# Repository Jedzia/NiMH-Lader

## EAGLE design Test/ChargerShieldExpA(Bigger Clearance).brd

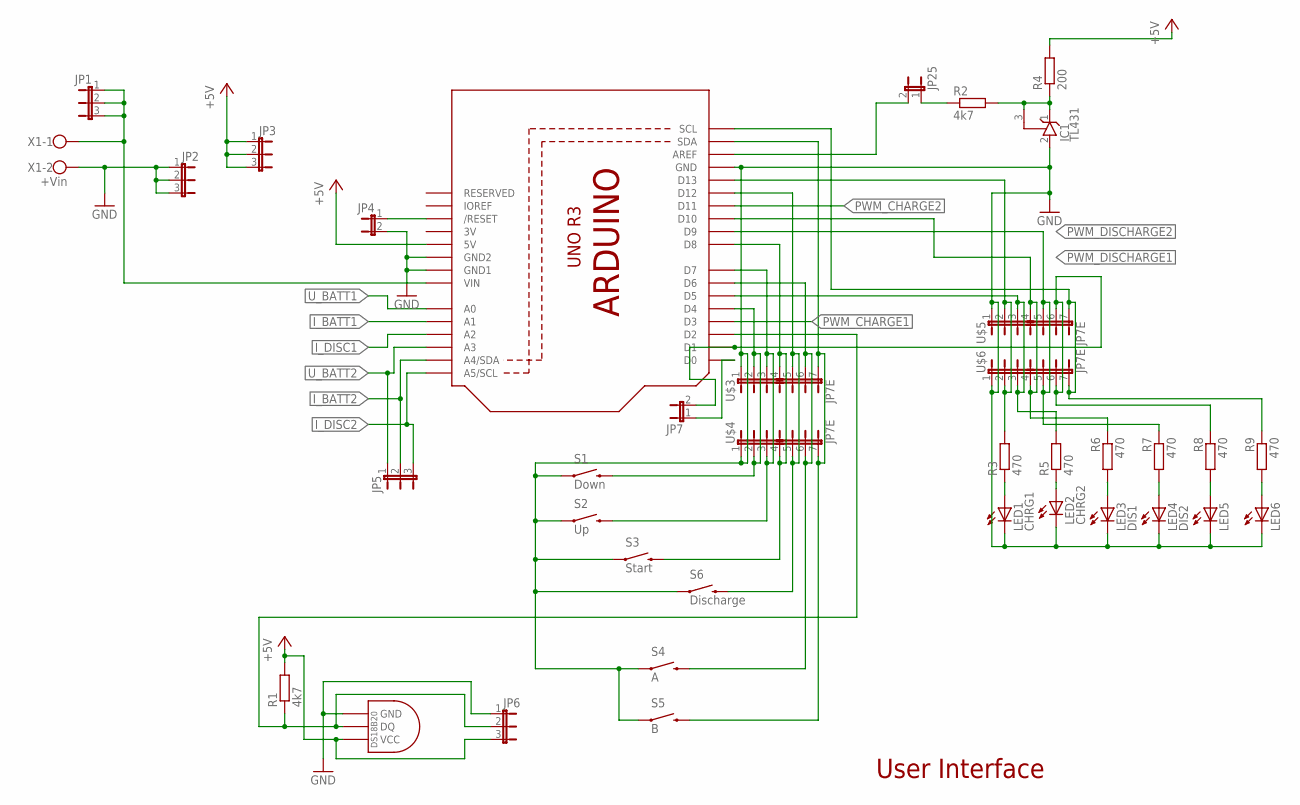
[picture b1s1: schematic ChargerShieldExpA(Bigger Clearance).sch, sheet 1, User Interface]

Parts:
IC1: TL431; TO92
JP1, JP2, JP3, JP5, JP6: JP2E; JP2
JP4, JP7, JP25: JP1E; JP1
LED1: CHRG1; LED5MM_BIG
LED2: CHRG2; LED5MM_BIG
LED3: DIS1; LED5MM_BIG
LED4: DIS2; LED5MM_BIG
LED5, LED6: LED5MM_BIG
R1: 4k7; 0204/7
R2: 4k7; 0207/10
R3: 470; 0207/12
R4: 200; 0204/7
R5, R6, R7: 470; 0207/10
R8, R9: 470; 0204/7
S1: Down; TACTILE-PTH-UMSE
S2: Up; TACTILE-PTH-UMSE
S3: Start; TACTILE-PTH-UMSE
S4: A; TACTILE-PTH-UMSE
S5: B; TACTILE-PTH-UMSE
S6: Discharge; TACTILE-PTH-UMSE
U$1: DS1820TO92; DS1820
U$2: ARDUINOR3BPLACE-LONG; ARDUINOR3-BPLACE-LONG
U$3, U$4, U$5, U$6: JP7E; JP7
X1: +Vin; W237-102

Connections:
3V: U$2.3V
+5V: JP3.1, JP3.2, JP3.3, JP6.3, R1.2, R4.2, U$1.VDD (VCC), U$2.5V; also elsewhere on the board
GND: IC1.2 (A), JP2.1, JP2.2, JP2.3, JP4.2, JP6.1, LED1.K (C), LED2.K (C), LED3.K (C), LED4.K (C), LED5.K (C), LED6.K (C), S1.1, S2.1, S3.1, S4.1, S5.1, S6.1, U$1.GND, U$2.GND, U$2.GND1, U$2.GND2, U$3.1, U$4.1, U$5.1, U$6.1, X1.2; also elsewhere on the board
I_BATT1: U$2.A1; also elsewhere on the board
I_BATT2: JP5.2, U$2.A4 (A4/SDA)
I_DISC1: U$2.A2; also elsewhere on the board
I_DISC2: JP5.3, U$2.A5 (A5/SCL)
unnamed: R3.2, U$2.D13, U$5.2, U$6.2
unnamed: LED1.A, R3.1
unnamed: JP6.2, R1.1, U$1.DQ, U$2.D2
unnamed: R5.2, U$2.D5, U$5.3, U$6.3
unnamed: LED3.A, R6.2
unnamed: LED4.A, R7.2
unnamed: S6.3 (2), U$2.D12, U$3.5, U$4.5
unnamed: LED2.A, R5.1
unnamed: S1.3 (2), U$2.D4, U$3.2, U$4.2
unnamed: IC1.1 (C), IC1.3 (R), R2.2, R4.1
unnamed: JP25.2, U$2.AREF
unnamed: S2.3 (2), U$2.D7, U$3.3, U$4.3
unnamed: S3.3 (2), U$2.D8, U$3.4, U$4.4
unnamed: S4.3 (2), U$2.D6, U$3.6, U$4.6
unnamed: S5.3 (2), U$2.SDA, U$3.7, U$4.7
unnamed: LED5.A, R8.2
unnamed: LED6.A, R9.2
unnamed: R9.1, U$2.SCL, U$5.7, U$6.7
unnamed: JP7.2, R8.1, U$2.D1, U$5.6, U$6.6
unnamed: JP7.1, U$2.D0
unnamed: JP4.1, U$2.RESET (/RESET)
unnamed: JP25.1, R2.1
PWM_CHARGE1: U$2.D3; also elsewhere on the board
PWM_CHARGE2: U$2.D11; also elsewhere on the board
PWM_DISCHARGE1: R6.1, U$2.D10, U$5.4, U$6.4; also elsewhere on the board
PWM_DISCHARGE2: R7.1, U$2.D9, U$5.5, U$6.5
U_BATT1: U$2.A0; also elsewhere on the board
U_BATT2: JP5.1, U$2.A3
VIN: JP1.1, JP1.2, JP1.3, U$2.VIN, X1.1; also elsewhere on the board

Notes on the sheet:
User Interface

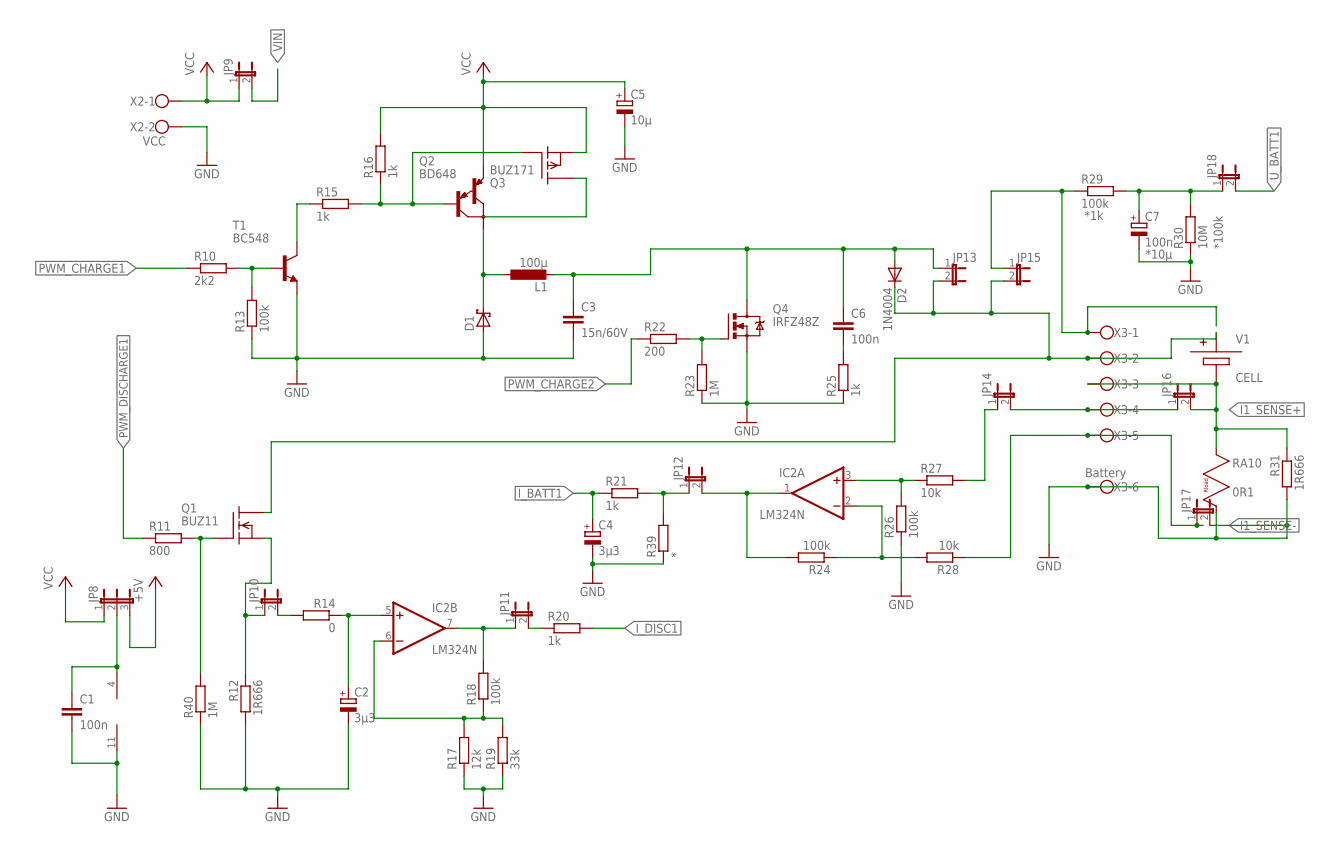
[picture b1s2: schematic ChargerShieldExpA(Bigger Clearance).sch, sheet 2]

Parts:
C1, C6: 100n; C025_050-025X075
C2, C4: 3µ3; E5-5
C3: 15n/60V; C025_050-025X075
C5: 10µ; E5-5
C7: 100n; E5-5
D1: SCHOTTKY-DIODEDO35-7; DO35-7
D2: 1N4004; DO41-10
IC2: LM324N; DIL14
JP8: JP2E; JP2
JP9, JP10, JP11, JP12, JP13, JP14, JP15, JP16, JP17, JP18: JP1E; JP1
L1: 100µ; 0207/12
Q1: BUZ11; TO220
Q2: BD648; TO220
Q3: BUZ171; TO220
Q4: IRFZ48Z; TO220BH
R10: 2k2; 0207/15
R11: 800; 0204/7
R12, R31: 1R666; 0414/15
R13, R18: 100k; 0207/10
R14: 0; 0207/10
R15, R16, R25: 1k; 0207/10
R17: 12k; 0207/10
R19: 33k; 0207/10
R20: 1k; 0207/15
R21: 1k; 0204/7
R22: 200; 0207/12
R23, R40: 1M; 0207/10
R24, R26: 100k; 0204/7
R27, R28: 10k; 0207/10
R29: 100k; 0207/12
R30: 10M; 0207/10
R39: *; 0204/7
T1: BC548; TO92
X2: VCC; W237-102
X3: Battery; W237-6

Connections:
+5V: JP8.3; also elsewhere on the board
GND: C1.2, C2.-, C3.2, C4.-, C5.-, C7.-, D1.A, IC2.11 (V-), JP17.2, Q4.S, R12.2, R13.1, R17.1, R19.1, R23.1, R25.1, R26.1, R30.1, R31.2, R39.1, R40.1, T1.1 (E), X2.2, X3.6; also elsewhere on the board
I1_SENSE+: JP16.2, R31.1, X3.3
I1_SENSE-: JP17.1, R28.1, X3.5
I_BATT1: C4.+, R21.1; also elsewhere on the board
I_DISC1: R20.2; also elsewhere on the board
unnamed: C7.+, JP18.1, R29.2, R30.2
unnamed: C1.1, IC2.4 (V+), JP8.2
unnamed: R10.2, R13.2, T1.2 (B)
unnamed: R15.1, T1.3 (C)
unnamed: Q2.1 (B), Q3.1 (G), R15.2, R16.1
unnamed: JP15.1, R29.1, X3.1
unnamed: D1.C, L1.1, Q2.2 (C)
unnamed: C3.1, C6.1, D2.A, JP13.1, L1.2, Q4.D
unnamed: IC2.1 (OUT), JP12.2, R24.2
unnamed: D2.C, JP13.2, JP15.2, Q1.2 (D), X3.2
unnamed: IC2.2 (-IN), R24.1, R28.2
unnamed: IC2.3 (+IN), R26.2, R27.1
unnamed: IC2.6 (-IN), R17.2, R18.1, R19.2
unnamed: IC2.7 (OUT), JP11.1, R18.2
unnamed: Q1.1 (G), R11.2, R40.2
unnamed: JP14.1, R27.2
unnamed: JP10.1, Q1.3 (S), R12.1
unnamed: C2.+, IC2.5 (+IN), R14.1
unnamed: JP12.1, R21.2, R39.2
unnamed: JP10.2, R14.2
unnamed: JP11.2, R20.1
unnamed: C6.2, R25.2
unnamed: Q4.G, R22.2, R23.2
unnamed: JP14.2, JP16.1, X3.4
PWM_CHARGE1: R10.1; also elsewhere on the board
PWM_CHARGE2: R22.1; also elsewhere on the board
PWM_DISCHARGE1: R11.1; also elsewhere on the board
U_BATT1: JP18.2; also elsewhere on the board
VCC: C5.+, JP8.1, JP9.1, Q2.3 (E), Q3.3 (S), R16.2, X2.1; also elsewhere on the board
VIN: JP9.2; also elsewhere on the board

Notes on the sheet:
*1k
*10µ
*100k

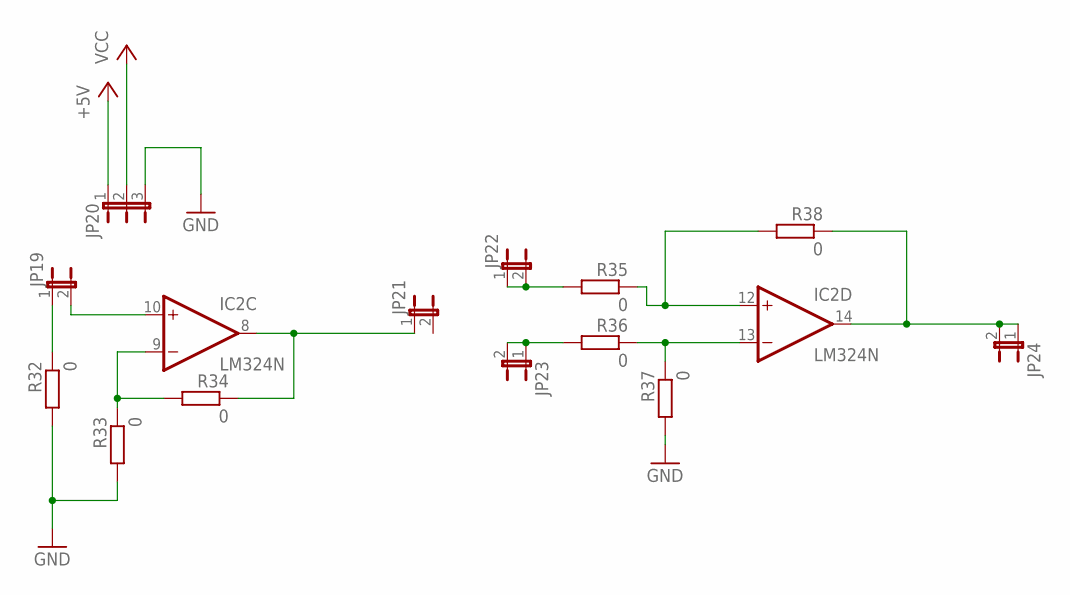
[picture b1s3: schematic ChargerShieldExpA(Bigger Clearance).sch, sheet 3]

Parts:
IC2: LM324N; DIL14
JP19, JP21, JP22, JP23, JP24: JP1E; JP1
JP20: JP2E; JP2
R32, R33, R36, R37, R38: 0; 0204/7
R34: 0; 0204V
R35: 0; 0207/10

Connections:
+5V: JP20.1; also elsewhere on the board
GND: JP20.3, R32.2, R33.2, R37.2; also elsewhere on the board
unnamed: IC2.8 (OUT), JP21.1, R34.1
unnamed: IC2.13 (-IN), R36.1, R37.1
unnamed: IC2.10 (+IN), JP19.2
unnamed: JP19.1, R32.1
unnamed: IC2.12 (+IN), R35.1, R38.2
unnamed: JP22.1, JP22.2, R35.2
unnamed: JP23.1, JP23.2, R36.2
unnamed: IC2.14 (OUT), JP24.1, JP24.2, R38.1
unnamed: IC2.9 (-IN), R33.1, R34.2
VCC: JP20.2; also elsewhere on the board

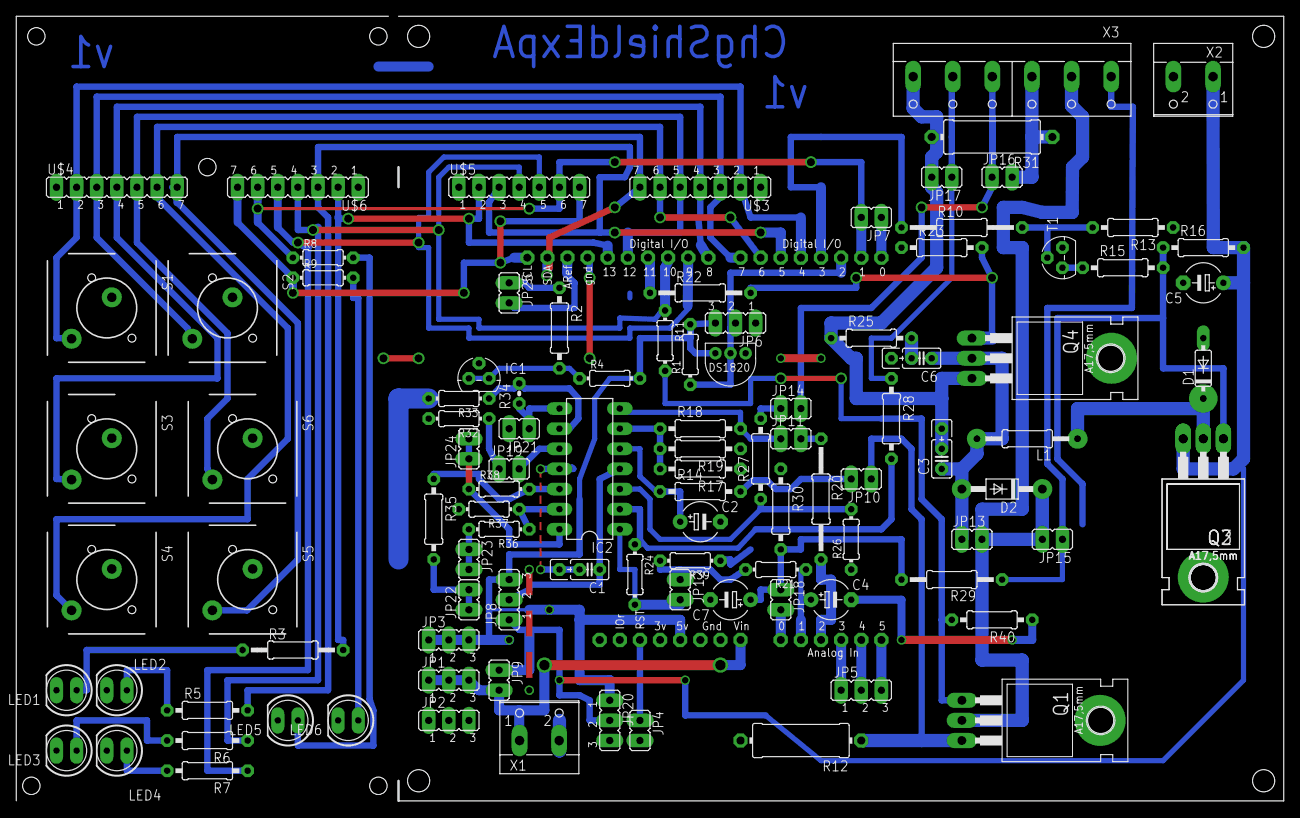
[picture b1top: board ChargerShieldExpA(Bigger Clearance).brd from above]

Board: 2 copper layers, 159.8 x 99.0 mm, 103 parts (0 on the bottom side), 71 nets.

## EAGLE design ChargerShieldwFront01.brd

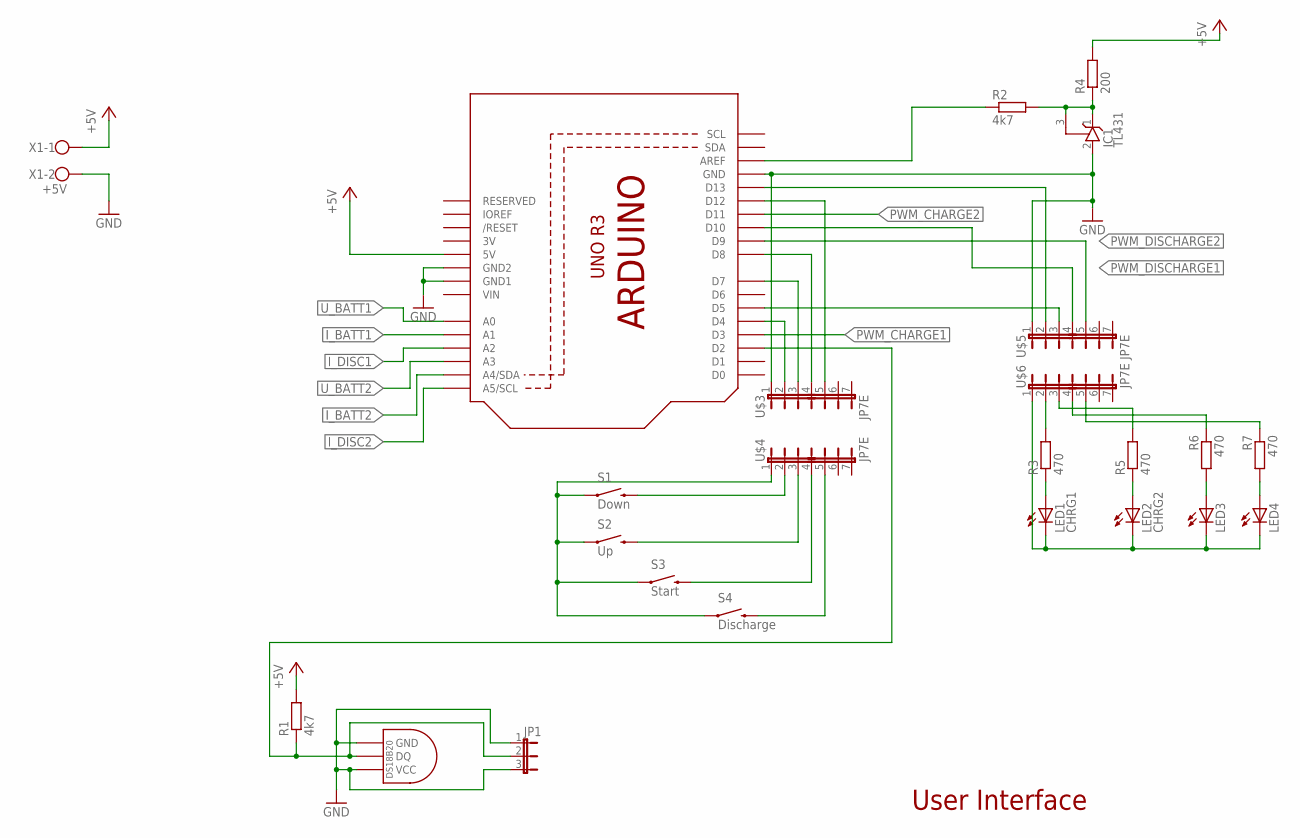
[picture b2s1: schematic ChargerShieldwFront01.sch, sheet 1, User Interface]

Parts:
IC1: TL431; TO92
JP1: JP2E; JP2
LED1: CHRG1; LED5MM_BIG
LED2: CHRG2; LED5MM_BIG
LED3, LED4: LED5MM_BIG
R1: 4k7; 0204/7
R2: 4k7; 0207/10
R3: 470; 0207/12
R4: 200; 0204/7
R5, R6, R7: 470; 0207/10
S1: Down; TACTILE-PTH
S2: Up; TACTILE-PTH
S3: Start; TACTILE-PTH
S4: Discharge; TACTILE-PTH
U$1: DS1820TO92; DS1820
U$2: ARDUINOR3BPLACE-LONG; ARDUINOR3-BPLACE-LONG
U$3, U$4, U$5, U$6: JP7E; JP7
X1: +5V; W237-102

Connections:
3V: U$2.3V
+5V: R1.2, R4.2, U$2.5V, X1.1; also elsewhere on the board
GND: IC1.2 (A), JP1.1, JP1.3, U$1.GND, U$1.VDD (VCC), U$2.GND, U$2.GND1, U$2.GND2, U$3.1, U$5.1, X1.2; also elsewhere on the board
GND2: LED1.K (C), LED2.K (C), LED3.K (C), LED4.K (C), S1.1, S2.1, S3.1, S4.1, U$4.1, U$6.1
I_BATT1: U$2.A1; also elsewhere on the board
I_BATT2: U$2.A4 (A4/SDA); also elsewhere on the board
I_DISC1: U$2.A2; also elsewhere on the board
I_DISC2: U$2.A5 (A5/SCL); also elsewhere on the board
unnamed: U$2.D13, U$5.2
unnamed: LED1.A, R3.1
unnamed: S1.3 (2), U$4.2
unnamed: S2.3 (2), U$4.3
unnamed: JP1.2, R1.1, U$1.DQ, U$2.D2
unnamed: U$2.D5, U$5.3
unnamed: LED3.A, R6.2
unnamed: LED4.A, R7.2
unnamed: S3.3 (2), U$4.4
unnamed: U$2.D12, U$3.5
unnamed: LED2.A, R5.1
unnamed: U$2.D4, U$3.2
unnamed: IC1.1 (C), IC1.3 (R), R2.2, R4.1
unnamed: R2.1, U$2.AREF
unnamed: U$2.D7, U$3.3
unnamed: U$2.D8, U$3.4
unnamed: S4.3 (2), U$4.5
unnamed: R5.2, U$6.3
unnamed: R3.2, U$6.2
unnamed: R6.1, U$6.4
unnamed: R7.1, U$6.5
PWM_CHARGE1: U$2.D3; also elsewhere on the board
PWM_CHARGE2: U$2.D11; also elsewhere on the board
PWM_DISCHARGE1: U$2.D10, U$5.4; also elsewhere on the board
PWM_DISCHARGE2: U$2.D9, U$5.5; also elsewhere on the board
U_BATT1: U$2.A0; also elsewhere on the board
U_BATT2: U$2.A3; also elsewhere on the board
VIN: U$2.VIN

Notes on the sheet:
User Interface

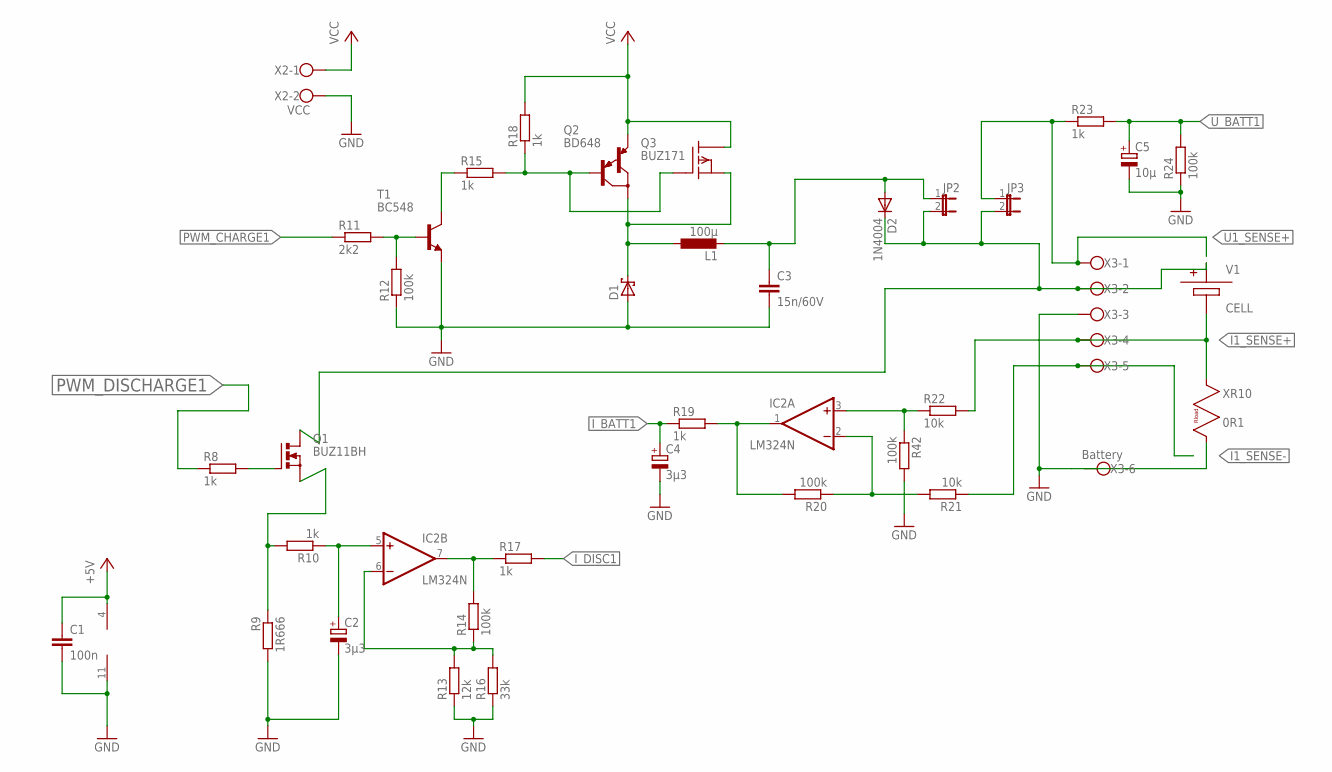
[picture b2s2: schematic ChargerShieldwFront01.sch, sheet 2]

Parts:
C1: 100n; C025_050-025X075
C2, C4: 3µ3; E5-5
C3: 15n/60V; C025_050-025X075
C5: 10µ; E5-5
D1: SCHOTTKY-DIODEDO35-7; DO35-7
D2: 1N4004; DO41-10
IC2: LM324N; DIL14
JP2, JP3: JP1E; JP1
L1: 100µ; 0207/12
Q1: BUZ11BH; TO220BH
Q2: BD648; TO220
Q3: BUZ171; TO220
R8, R19: 1k; 0207/12
R9: 1R666; 0414/15
R10, R15, R18, R23: 1k; 0207/10
R11: 2k2; 0207/10
R12, R20, R42: 100k; 0204/7
R13: 12k; 0207/10
R14, R24: 100k; 0207/10
R16: 33k; 0207/10
R17: 1k; 0207/15
R21: 10k; 0207/12
R22: 10k; 0207/10
T1: BC548; TO92
X2: VCC; W237-102
X3: Battery; W237-6

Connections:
+5V: C1.1, IC2.4 (V+); also elsewhere on the board
GND: C1.2, C2.-, C3.2, C4.-, C5.-, D1.A, IC2.11 (V-), R9.2, R12.1, R13.1, R16.1, R24.1, R42.2, T1.1 (E), X2.2, X3.3, X3.6; also elsewhere on the board
I1_SENSE+: R22.2, X3.4
I1_SENSE-: R21.1, X3.5
I_BATT1: C4.+, R19.1; also elsewhere on the board
I_DISC1: R17.2; also elsewhere on the board
unnamed: R11.2, R12.2, T1.2 (B)
unnamed: R15.1, T1.3 (C)
unnamed: Q2.1 (B), Q3.1 (G), R15.2, R18.1
unnamed: D1.C, L1.1, Q2.2 (C), Q3.3 (S)
unnamed: C3.1, D2.A, JP2.1, L1.2
unnamed: IC2.1 (OUT), R19.2, R20.2
unnamed: D2.C, JP2.2, JP3.2, Q1.D, X3.2
unnamed: IC2.2 (-IN), R20.1, R21.2
unnamed: IC2.3 (+IN), R22.1, R42.1
unnamed: IC2.6 (-IN), R13.2, R14.1, R16.2
unnamed: IC2.7 (OUT), R14.2, R17.1
unnamed: Q1.G, R8.2
unnamed: Q1.S, R9.1, R10.2
unnamed: C2.+, IC2.5 (+IN), R10.1
PWM_CHARGE1: R11.1; also elsewhere on the board
PWM_DISCHARGE1: R8.1; also elsewhere on the board
U1_SENSE+: JP3.1, R23.1, X3.1
U_BATT1: C5.+, R23.2, R24.2; also elsewhere on the board
VCC: Q2.3 (E), Q3.2 (D), R18.2, X2.1; also elsewhere on the board

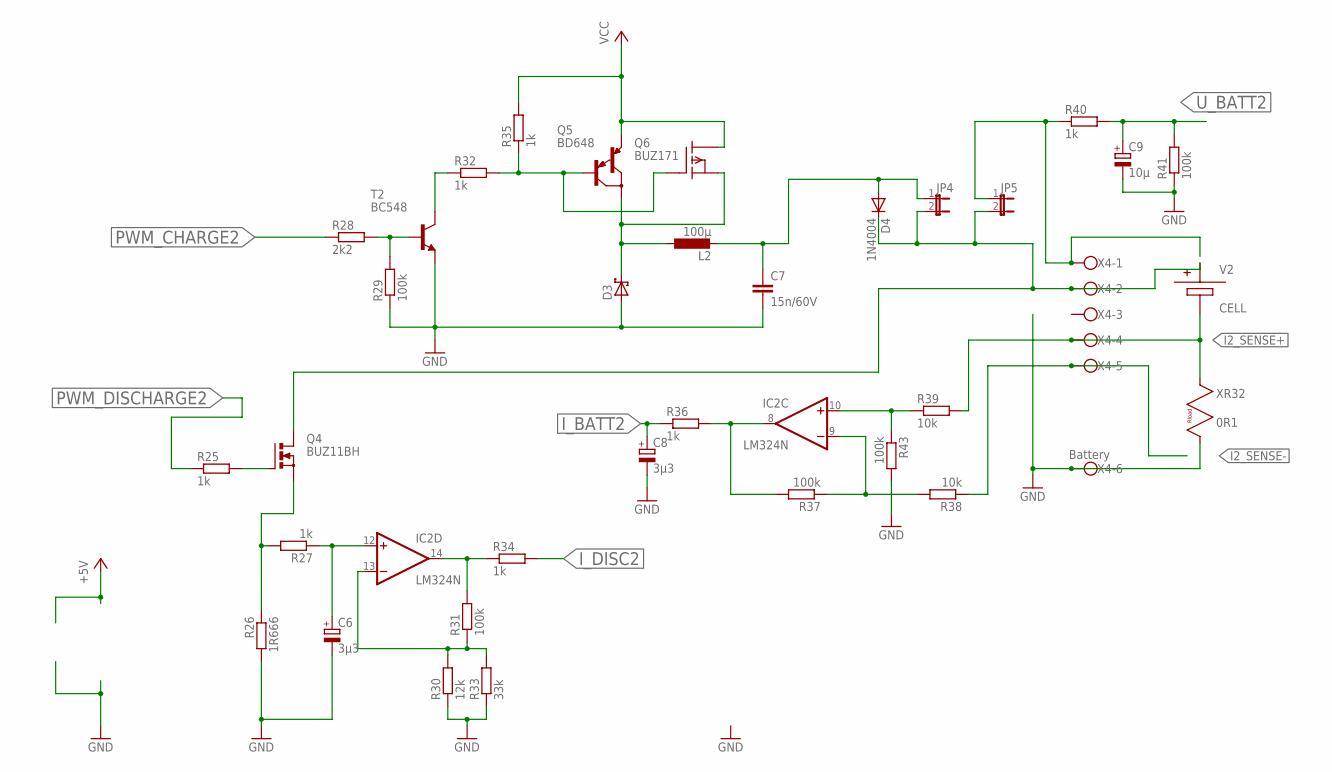
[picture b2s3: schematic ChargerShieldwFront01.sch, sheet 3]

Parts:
C6, C8: 3µ3; E5-5
C7: 15n/60V; C025_050-025X075
C9: 10µ; E5-5
D3: SCHOTTKY-DIODEDO35-7; DO35-7
D4: 1N4004; DO41-10
IC2: LM324N; DIL14
JP4, JP5: JP1E; JP1
L2: 100µ; 0207/12
Q4: BUZ11BH; TO220BH
Q5: BD648; TO220
Q6: BUZ171; TO220
R25, R32, R35, R40: 1k; 0207/10
R26: 1R666; 0414/15
R27, R36: 1k; 0207/12
R28: 2k2; 0207/15
R29, R37: 100k; 0204/7
R30: 12k; 0207/10
R31, R41, R43: 100k; 0207/10
R33: 33k; 0207/10
R34: 1k; 0207/15
R38: 10k; 0207/15
R39: 10k; 0207/10
T2: BC548; TO92
X4: Battery; W237-6

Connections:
GND: C6.-, C7.2, C8.-, C9.-, D3.A, R26.2, R29.1, R30.1, R33.1, R41.1, R43.2, T2.1 (E), X4.6; also elsewhere on the board
I2_SENSE+: R39.2, X4.4
I2_SENSE-: R38.1, X4.5
I_BATT2: C8.+, R36.1; also elsewhere on the board
I_DISC2: R34.2; also elsewhere on the board
unnamed: R28.2, R29.2, T2.2 (B)
unnamed: R32.1, T2.3 (C)
unnamed: Q5.1 (B), Q6.1 (G), R32.2, R35.1
unnamed: D3.C, L2.1, Q5.2 (C), Q6.3 (S)
unnamed: C7.1, D4.A, JP4.1, L2.2
unnamed: IC2.8 (OUT), R36.2, R37.2
unnamed: IC2.9 (-IN), R37.1, R38.2
unnamed: D4.C, JP4.2, JP5.2, Q4.D, X4.2
unnamed: JP5.1, R40.1, X4.1
unnamed: IC2.10 (+IN), R39.1, R43.1
unnamed: IC2.13 (-IN), R30.2, R31.1, R33.2
unnamed: IC2.14 (OUT), R31.2, R34.1
unnamed: Q4.G, R25.2
unnamed: Q4.S, R26.1, R27.2
unnamed: C6.+, IC2.12 (+IN), R27.1
PWM_CHARGE2: R28.1; also elsewhere on the board
PWM_DISCHARGE2: R25.1; also elsewhere on the board
U_BATT2: C9.+, R40.2, R41.2; also elsewhere on the board
VCC: Q5.3 (E), Q6.2 (D), R35.2; also elsewhere on the board

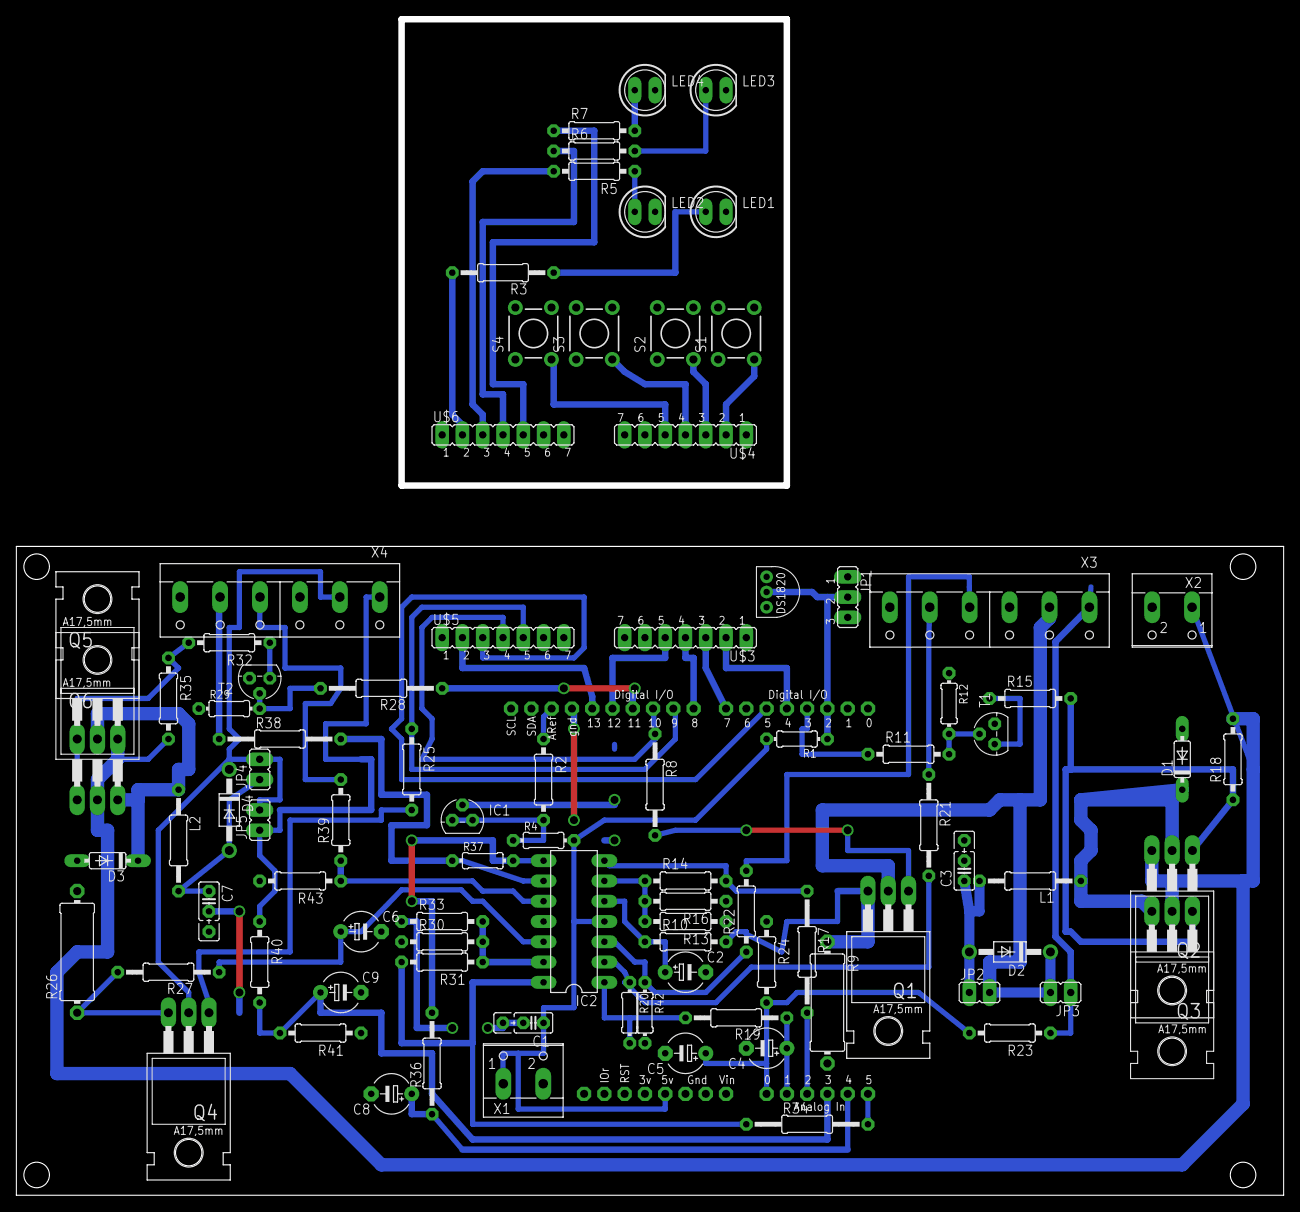
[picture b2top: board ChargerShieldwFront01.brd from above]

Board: 2 copper layers, 158.0 x 147.0 mm, 91 parts (0 on the bottom side), 69 nets.

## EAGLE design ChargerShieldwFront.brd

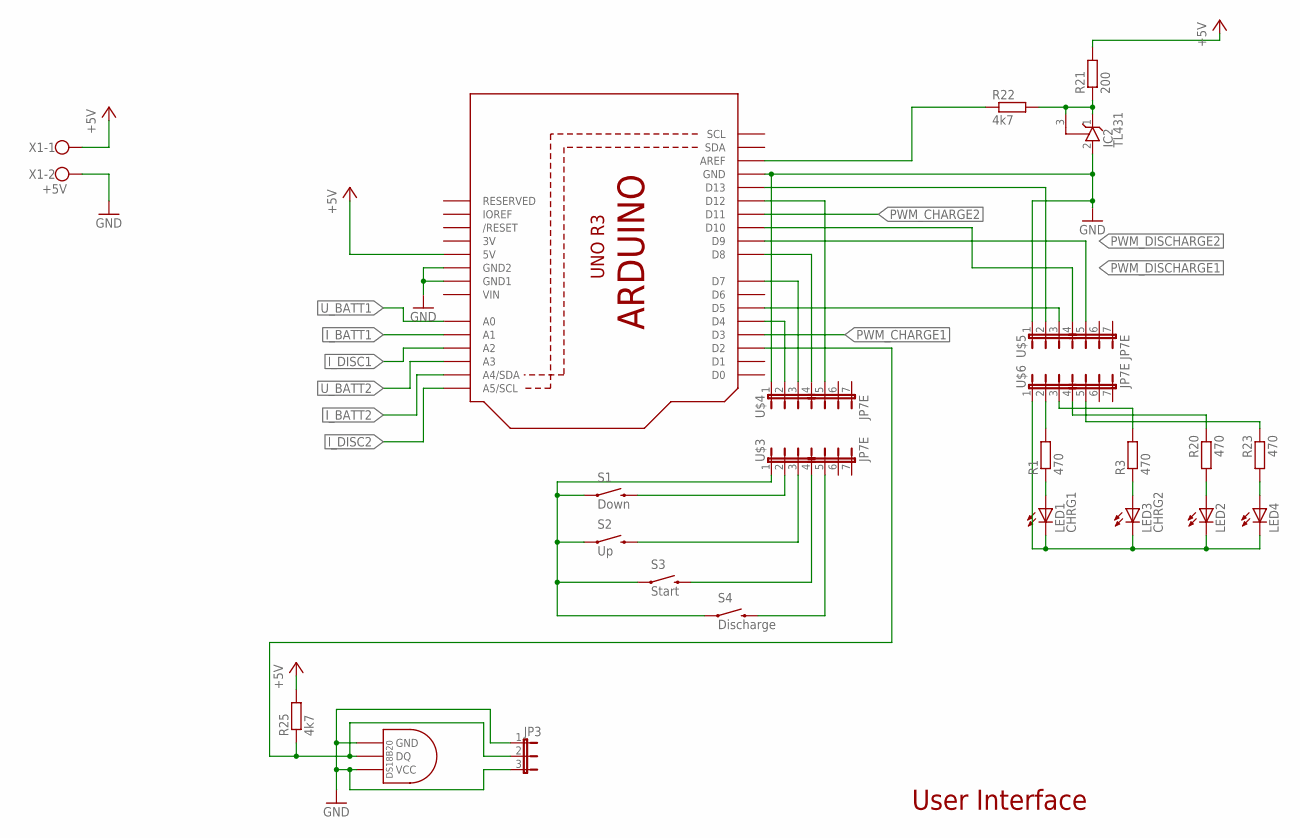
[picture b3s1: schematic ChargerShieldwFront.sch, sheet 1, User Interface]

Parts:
IC2: TL431; TO92
JP3: JP2E; JP2
LED1: CHRG1; LED5MM_BIG
LED2, LED4: LED5MM_BIG
LED3: CHRG2; LED5MM_BIG
R1: 470; 0207/12
R3, R20, R23: 470; 0207/10
R21: 200; 0204/7
R22: 4k7; 0207/10
R25: 4k7; 0204/7
S1: Down; TACTILE-PTH
S2: Up; TACTILE-PTH
S3: Start; TACTILE-PTH
S4: Discharge; TACTILE-PTH
U$1: ARDUINOR3BPLACE-LONG; ARDUINOR3-BPLACE-LONG
U$2: DS1820TO92; DS1820
U$3, U$4, U$5, U$6: JP7E; JP7
X1: +5V; W237-102

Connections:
3V: U$1.3V
+5V: R21.2, R25.2, U$1.5V, X1.1; also elsewhere on the board
GND: IC2.2 (A), JP3.1, JP3.3, U$1.GND, U$1.GND1, U$1.GND2, U$2.GND, U$2.VDD (VCC), U$4.1, U$5.1, X1.2; also elsewhere on the board
GND2: LED1.K (C), LED2.K (C), LED3.K (C), LED4.K (C), S1.1, S2.1, S3.1, S4.1, U$3.1, U$6.1
I_BATT1: U$1.A1; also elsewhere on the board
I_BATT2: U$1.A4 (A4/SDA)
I_DISC1: U$1.A2; also elsewhere on the board
I_DISC2: U$1.A5 (A5/SCL)
unnamed: U$1.D13, U$5.2
unnamed: LED1.A, R1.1
unnamed: S1.3 (2), U$3.2
unnamed: S2.3 (2), U$3.3
unnamed: JP3.2, R25.1, U$1.D2, U$2.DQ
unnamed: U$1.D5, U$5.3
unnamed: LED2.A, R20.2
unnamed: LED4.A, R23.2
unnamed: S3.3 (2), U$3.4
unnamed: U$1.D12, U$4.5
unnamed: LED3.A, R3.1
unnamed: U$1.D4, U$4.2
unnamed: IC2.1 (C), IC2.3 (R), R21.1, R22.2
unnamed: R22.1, U$1.AREF
unnamed: U$1.D7, U$4.3
unnamed: U$1.D8, U$4.4
unnamed: S4.3 (2), U$3.5
unnamed: R3.2, U$6.3
unnamed: R1.2, U$6.2
unnamed: R20.1, U$6.4
unnamed: R23.1, U$6.5
PWM_CHARGE1: U$1.D3; also elsewhere on the board
PWM_CHARGE2: U$1.D11
PWM_DISCHARGE1: U$1.D10, U$5.4; also elsewhere on the board
PWM_DISCHARGE2: U$1.D9, U$5.5
U_BATT1: U$1.A0; also elsewhere on the board
U_BATT2: U$1.A3
VIN: U$1.VIN

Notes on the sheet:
User Interface

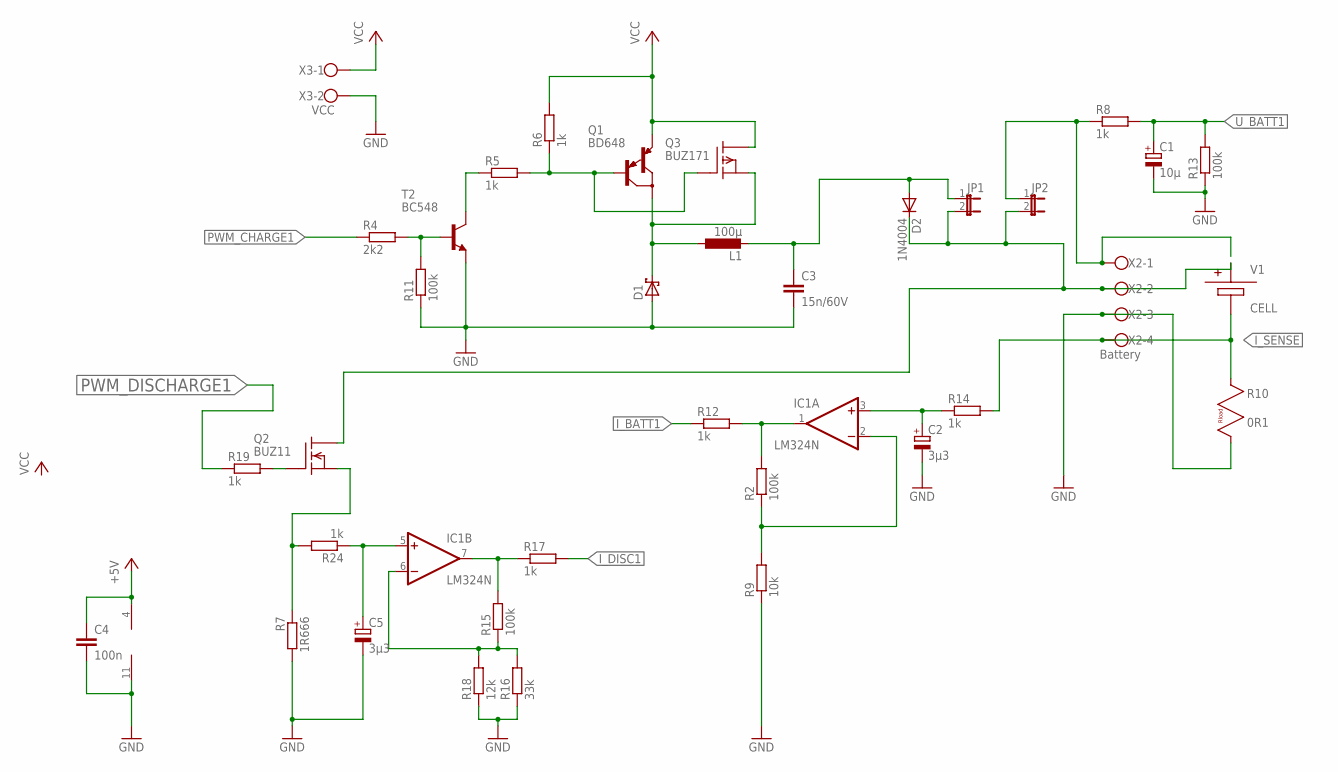
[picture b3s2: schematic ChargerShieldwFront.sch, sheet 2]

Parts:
C1: 10µ; E5-5
C2, C5: 3µ3; E5-5
C3: 15n/60V; C025_050-025X075
C4: 100n; C025_050-025X075
D1: SCHOTTKY-DIODEDO35-7; DO35-7
D2: 1N4004; DO41-10
IC1: LM324N; DIL14
JP1, JP2: JP1E; JP1
L1: 100µ; 0207/12
Q1: BD648; TO220
Q2: BUZ11; TO220
Q3: BUZ171; TO220
R2: 100k; 0204/7
R4: 2k2; 0207/10
R5, R6, R8, R14, R24: 1k; 0207/10
R7: 1R666; 0414/15
R9: 10k; 0204/7
R11, R13, R15: 100k; 0207/10
R12, R19: 1k; 0207/12
R16: 33k; 0207/10
R17: 1k; 0207/15
R18: 12k; 0207/10
T2: BC548; TO92
X2: Battery; W237-4
X3: VCC; W237-102

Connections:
+5V: C4.1, IC1.4 (V+); also elsewhere on the board
GND: C1.-, C2.-, C3.2, C4.2, C5.-, D1.A, IC1.11 (V-), R7.2, R9.1, R11.1, R13.1, R16.1, R18.1, T2.1 (E), X2.3, X3.2; also elsewhere on the board
I_BATT1: R12.1; also elsewhere on the board
I_DISC1: R17.2; also elsewhere on the board
I_SENSE: R14.2, X2.4
unnamed: R4.2, R11.2, T2.2 (B)
unnamed: R5.1, T2.3 (C)
unnamed: Q1.1 (B), Q3.1 (G), R5.2, R6.1
unnamed: JP2.1, R8.1, X2.1
unnamed: D1.C, L1.1, Q1.2 (C), Q3.3 (S)
unnamed: C3.1, D2.A, JP1.1, L1.2
unnamed: IC1.1 (OUT), R2.2, R12.2
unnamed: D2.C, JP1.2, JP2.2, Q2.2 (D), X2.2
unnamed: IC1.2 (-IN), R2.1, R9.2
unnamed: C2.+, IC1.3 (+IN), R14.1
unnamed: IC1.6 (-IN), R15.1, R16.2, R18.2
unnamed: IC1.7 (OUT), R15.2, R17.1
unnamed: Q2.1 (G), R19.2
unnamed: Q2.3 (S), R7.1, R24.2
unnamed: C5.+, IC1.5 (+IN), R24.1
PWM_CHARGE1: R4.1; also elsewhere on the board
PWM_DISCHARGE1: R19.1; also elsewhere on the board
U_BATT1: C1.+, R8.2, R13.2; also elsewhere on the board
VCC: Q1.3 (E), Q3.2 (D), R6.2, X3.1

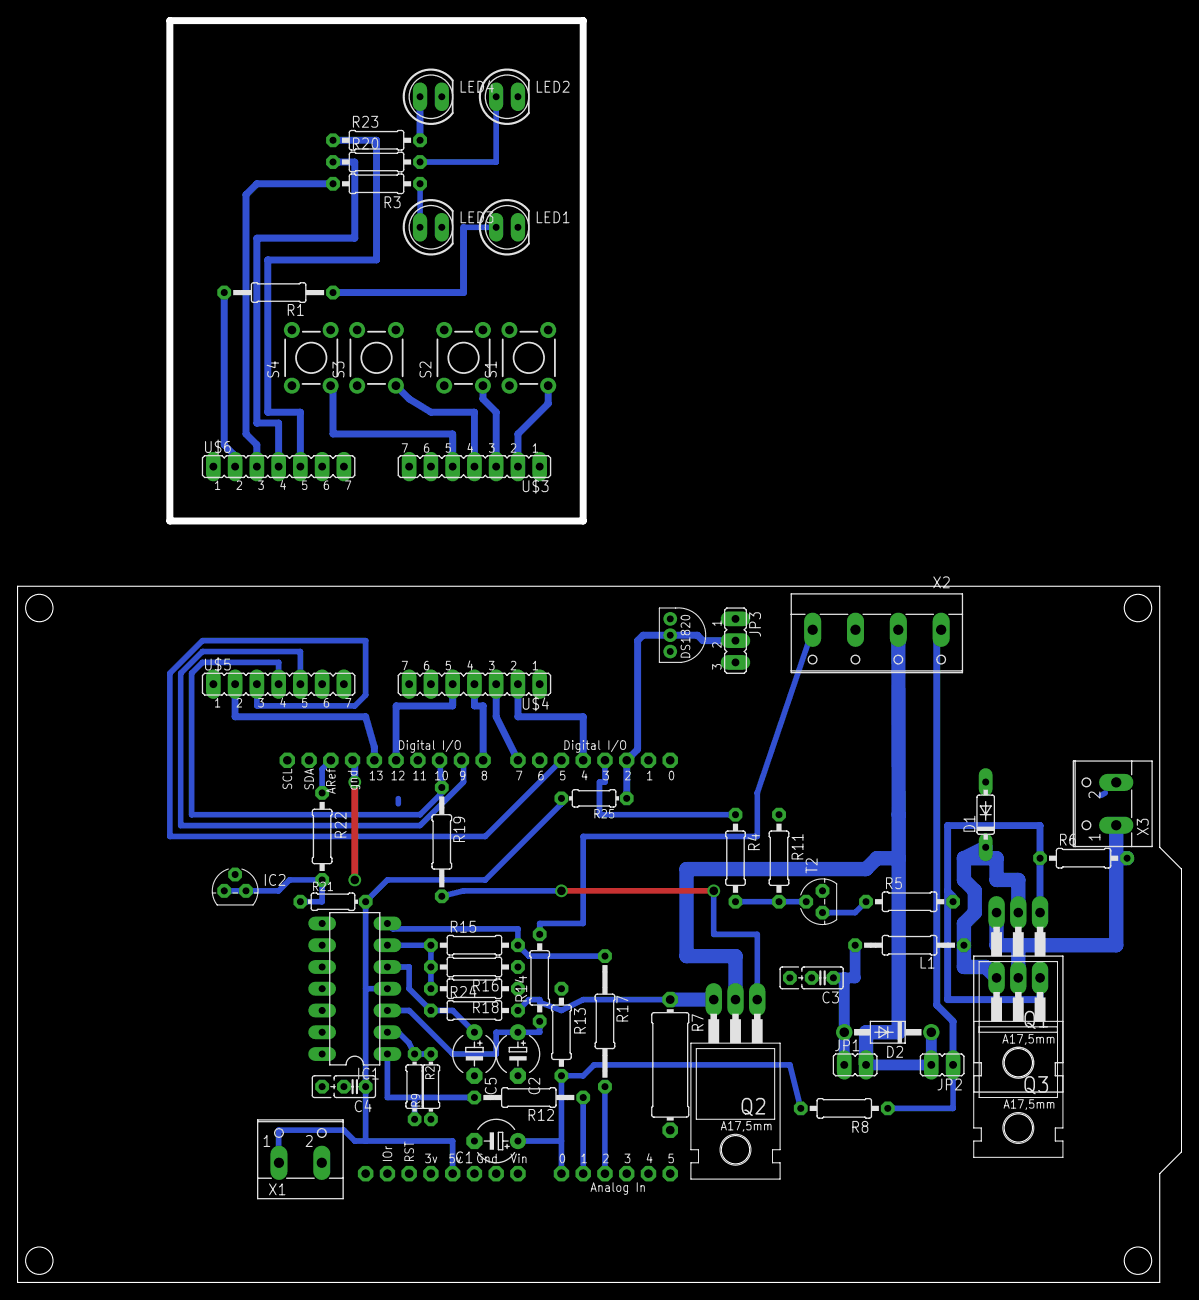
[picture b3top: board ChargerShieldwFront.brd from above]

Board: 2 copper layers, 135.2 x 147.0 mm, 58 parts (0 on the bottom side), 47 nets.

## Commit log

2014-11-27 Initial check in.
2014-11-27 added software and board
2014-11-29 current sense
2014-11-29 start button and current sense program
2014-11-30 100kHz and manual PWM mode.
2014-11-30 smaller diode
2014-11-30 Discharge
2014-12-01 | in messages, shortened analog read delay
2014-12-01 app state
2014-12-01 all appState
2014-12-01 only stop end voltage at charging state
2014-12-02 faster current control.
2014-12-02 longer Arduino shield
2014-12-02 LM324
2014-12-02 changes to reflect current breadboard layout
2014-12-02 - debug messages via preprocessor. - PWMMAX for secure testing set to 60.
2014-12-02 some constants and test data
2014-12-03 trend
2014-12-05 charge/discharge voltage trend over time
2014-12-05 more trendy
2014-12-05 temperature trend shut off
2014-12-07 delta U fine tuning
2014-12-07 maxVoltage times to kick in delta U
2014-12-08 capacity calculation
2014-12-08 measure time correction for capacity calculation.
2014-12-09 reference voltage
2014-12-09 bigger power traces
2014-12-10 bigger board
2014-12-10 with front board
2014-12-14 detect and display One Wire Bus Mode
2014-12-14 second charge part
2014-12-14 thicker wires
2014-12-15 single test version with front
2014-12-15 reusable front panel
2014-12-15 front board interconnections
2014-12-15 opamp test circuitry
2014-12-16 before diff
2014-12-16 difference amplifier at charge current
2014-12-17 all I_batt differential
2014-12-17 arrangement
2014-12-18 power pins, Vin
2014-12-18 boost converter
2014-12-18 tidy up
2014-12-18 internal current sense shunt
2014-12-18 first layout
2014-12-18 renumbered
2014-12-19 before production
2014-12-19 Production version v1
2014-12-20 rearranged, better DRC
2014-12-20 via drills should be 1mm
2014-12-21 V1 Production review
2014-12-23 - PROTOTYPE_BOARD define for prototype board use. - wrong FET connections
2014-12-23 display adjustment
2014-12-24 Higher input impedance for U_Batt
2014-12-24 TEMP_MAX, TEMP_DELTA_MAX, PWMSENSORTOLERANCE, PWMUPDOWNSTEP constants
2014-12-24 more updates for the state buttons
2014-12-24 - more updates for the up/down buttons. - finer current setpoint adjustment.
2014-12-25 fixed S5, S6
2014-12-25 BuckBoost
2014-12-25 correct dischargePWM1Pin
2015-01-02 Expansion board with LCD Pinout
2015-01-04 rearranged power transistors
2015-01-05 jumper to switch LCD RS Pin
2015-01-10 Soft
2015-01-10 some sort of logging
2015-11-24 testing out bigger clearance for GND Layer
2016-10-07 Moin Holger;)
2016-10-07 use Time lib correctly. so it works in arduino ide 1.6.12

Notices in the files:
parts and their libraries:
SparkFun-Electromechanical: Licensing: Creative Commons ShareAlike 4.0 International - https://creativecommons.org/licenses/by-sa/4.0
